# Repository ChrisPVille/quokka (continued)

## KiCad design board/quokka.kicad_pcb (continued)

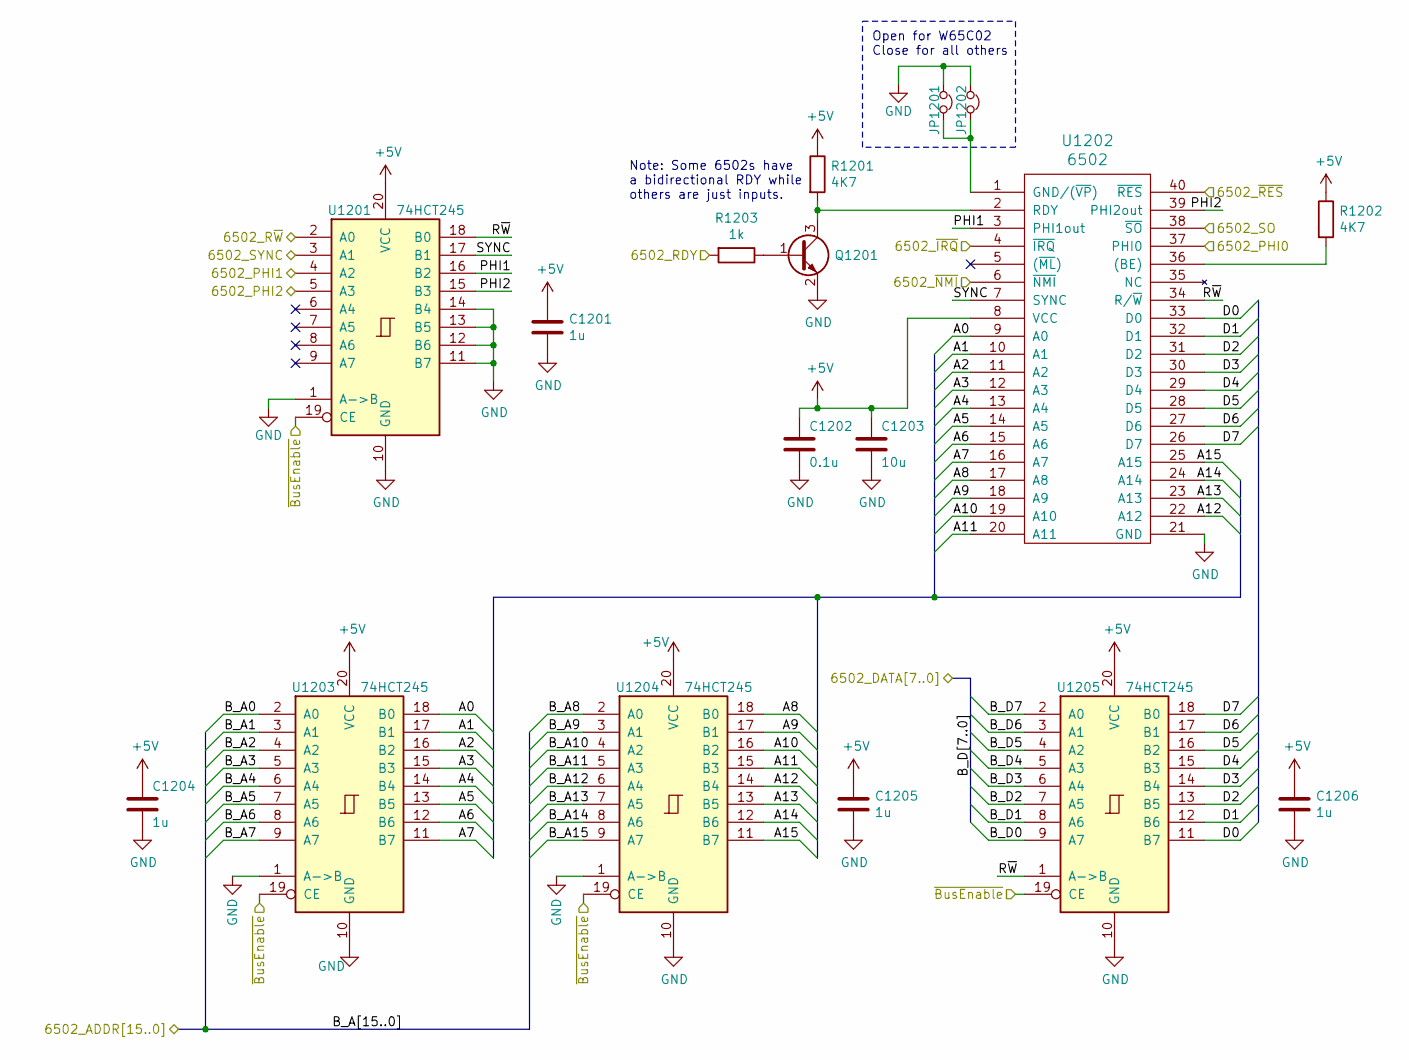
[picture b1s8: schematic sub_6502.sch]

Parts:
C1201, C1204, C1205, C1206: 1u; C_0603_1608Metric
C1202: 0.1u; C_0603_1608Metric
C1203: 10u; C_1206_3216Metric
JP1201: Jumper_NC_Small; PinHeader_1x02_P2.54mm_Vertical
JP1202: WireJumper; PinHeader_1x02_P2.54mm_Vertical
Q1201: Q_NPN_BEC; SOT-23
R1201, R1202: 4K7; R_0603_1608Metric
R1203: 1k; R_0603_1608Metric
U1201, U1203, U1204, U1205: 74HCT245; SSOP-20_4.4x6.5mm_P0.65mm
U1202: 6502; DIP-40_W15.24mm

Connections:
+5V: C1201.1, C1202.1, C1203.1, C1204.1, C1205.1, C1206.1, R1201.1, R1202.1, U1201.20 (VCC), U1202.8 (VCC), U1203.20 (VCC), U1204.20 (VCC), U1205.20 (VCC); also elsewhere on the board
/6502/6502_PHI0: U1202.37 (PHI0); also elsewhere on the board
/6502/6502_PHI1: U1201.4 (A2); also elsewhere on the board
/6502/6502_PHI2: U1201.5 (A3); also elsewhere on the board
/6502/6502_RDY: R1203.2; also elsewhere on the board
/6502/6502_R~W: U1201.2 (A0); also elsewhere on the board
/6502/6502_SO: U1202.38 (~SO); also elsewhere on the board
/6502/6502_SYNC: U1201.3 (A1); also elsewhere on the board
/6502/6502_~IRQ: U1202.4 (~IRQ); also elsewhere on the board
/6502/6502_~NMI: U1202.6 (~NMI); also elsewhere on the board
/6502/6502_~RES: U1202.40 (~RES); also elsewhere on the board
/6502/A0: U1202.9 (A0), U1203.18 (B0)
/6502/A1: U1202.10 (A1), U1203.17 (B1)
/6502/A2: U1202.11 (A2), U1203.16 (B2)
/6502/A3: U1202.12 (A3), U1203.15 (B3)
/6502/A4: U1202.13 (A4), U1203.14 (B4)
/6502/A5: U1202.14 (A5), U1203.13 (B5)
/6502/A6: U1202.15 (A6), U1203.12 (B6)
/6502/A7: U1202.16 (A7), U1203.11 (B7)
/6502/A8: U1202.17 (A8), U1204.18 (B0)
/6502/A9: U1202.18 (A9), U1204.17 (B1)
/6502/A10: U1202.19 (A10), U1204.16 (B2)
/6502/A11: U1202.20 (A11), U1204.15 (B3)
/6502/A12: U1202.22 (A12), U1204.14 (B4)
/6502/A13: U1202.23 (A13), U1204.13 (B5)
/6502/A14: U1202.24 (A14), U1204.12 (B6)
/6502/A15: U1202.25 (A15), U1204.11 (B7)
/6502/B_D0: U1205.9 (A7); also elsewhere on the board
/6502/B_D1: U1205.8 (A6); also elsewhere on the board
/6502/B_D2: U1205.7 (A5); also elsewhere on the board
/6502/B_D3: U1205.6 (A4); also elsewhere on the board
/6502/B_D4: U1205.5 (A3); also elsewhere on the board
/6502/B_D5: U1205.4 (A2); also elsewhere on the board
/6502/B_D6: U1205.3 (A1); also elsewhere on the board
/6502/B_D7: U1205.2 (A0); also elsewhere on the board
/6502/D0: U1202.33 (D0), U1205.11 (B7)
/6502/D1: U1202.32 (D1), U1205.12 (B6)
/6502/D2: U1202.31 (D2), U1205.13 (B5)
/6502/D3: U1202.30 (D3), U1205.14 (B4)
/6502/D4: U1202.29 (D4), U1205.15 (B3)
/6502/D5: U1202.28 (D5), U1205.16 (B2)
/6502/D6: U1202.27 (D6), U1205.17 (B1)
/6502/D7: U1202.26 (D7), U1205.18 (B0)
/6502/PHI1: U1201.16 (B2), U1202.3 (PHI1out)
/6502/PHI2: U1201.15 (B3), U1202.39 (PHI2out)
/6502/R~W: U1201.18 (B0), U1202.34 (R/~W), U1205.1 (A->B)
/6502/SYNC: U1201.17 (B1), U1202.7 (SYNC)
/Bus Expansion/A0: U1203.2 (A0); also elsewhere on the board
/Bus Expansion/A1: U1203.3 (A1); also elsewhere on the board
/Bus Expansion/A2: U1203.4 (A2); also elsewhere on the board
/Bus Expansion/A3: U1203.5 (A3); also elsewhere on the board
/Bus Expansion/A4: U1203.6 (A4); also elsewhere on the board
/Bus Expansion/A5: U1203.7 (A5); also elsewhere on the board
/Bus Expansion/A6: U1203.8 (A6); also elsewhere on the board
/Bus Expansion/A7: U1203.9 (A7); also elsewhere on the board
/Bus Expansion/A8: U1204.2 (A0); also elsewhere on the board
/Bus Expansion/A9: U1204.3 (A1); also elsewhere on the board
/Bus Expansion/A10: U1204.4 (A2); also elsewhere on the board
/Bus Expansion/A11: U1204.5 (A3); also elsewhere on the board
/Bus Expansion/A12: U1204.6 (A4); also elsewhere on the board
/Bus Expansion/A13: U1204.7 (A5); also elsewhere on the board
/Bus Expansion/A14: U1204.8 (A6); also elsewhere on the board
/Bus Expansion/A15: U1204.9 (A7); also elsewhere on the board
/FPGA/Physical6502_~BusEnable: U1201.19 (CE), U1203.19 (CE), U1204.19 (CE), U1205.19 (CE); also elsewhere on the board
GND: C1201.2, C1202.2, C1203.2, C1204.2, C1205.2, C1206.2, JP1201.1, JP1202.1, Q1201.2 (E), U1201.1 (A->B), U1201.10 (GND), U1201.11 (B7), U1201.12 (B6), U1201.13 (B5), U1201.14 (B4), U1202.21 (GND), U1203.1 (A->B), U1203.10 (GND), U1204.1 (A->B), U1204.10 (GND), U1205.10 (GND); also elsewhere on the board
unnamed: JP1201.2, JP1202.2, U1202.1 (GND/(~VP~))
unnamed: Q1201.1 (B), R1203.1
unnamed: Q1201.3 (C), R1201.2, U1202.2 (RDY)
unnamed: R1202.2, U1202.36 ((BE))

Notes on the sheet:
Open for W65C02 Close for all others
Note: Some 6502s have a bidirectional RDY while others are just inputs.

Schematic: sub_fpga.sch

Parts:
C1301: 0.1u; C_0603_1608Metric
J1301: FPGA JTAG; PinHeader_1x06_P2.54mm_Vertical
Q1301: Q_NPN_BEC; SOT-23
R1301, R1304: 4K7; R_0603_1608Metric
R1302: 390; R_0603_1608Metric
R1303, R1306: 68; R_0603_1608Metric
R1305: 1k; R_0603_1608Metric
U205: XC3S200-TQ144; LQFP-144_20x20mm_P0.5mm
X1301: SG7050CAN 25.0Mhz; Oscillator_SMD_SeikoEpson_SG8002CA-4Pin_7.0x5.0mm

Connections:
+2V5: J1301.6, R1302.2, U205.37 (M1), U205.38 (M0), U205.39 (M2); also elsewhere on the board
/Bus Expansion/E0: U205.27 (IO_L22P_6); also elsewhere on the board
/Bus Expansion/E1: U205.28 (IO_L22N_6); also elsewhere on the board
/Bus Expansion/E2: U205.30 (IO_L21P_6); also elsewhere on the board
/Bus Expansion/E3: U205.31 (IO_L21N_6); also elsewhere on the board
/Bus Expansion/E4: U205.32 (IO_L20P_6); also elsewhere on the board
/Bus Expansion/E5: U205.33 (IO_L20N_6); also elsewhere on the board
/Bus Expansion/E6: U205.35 (IO_L01P_6/VRN_6); also elsewhere on the board
/Bus Expansion/E7: U205.36 (IO_L01N_6/VRP_6); also elsewhere on the board
/FPGA/A0: U205.108 (IO_L01N_2/VRP_2); also elsewhere on the board
/FPGA/A1: U205.107 (IO_L01P_2/VRN_2); also elsewhere on the board
/FPGA/A2: U205.105 (IO_L20N_2); also elsewhere on the board
/FPGA/A3: U205.104 (IO_L20P_2); also elsewhere on the board
/FPGA/A4: U205.103 (IO_L21N_2); also elsewhere on the board
/FPGA/A5: U205.102 (IO_L21P_2); also elsewhere on the board
/FPGA/A6: U205.100 (IO_L22N_2); also elsewhere on the board
/FPGA/A7: U205.99 (IO_L22P_2); also elsewhere on the board
/FPGA/A8: U205.98 (IO_L23N_2/VREF_2); also elsewhere on the board
/FPGA/A9: U205.97 (IO_L23P_2); also elsewhere on the board
/FPGA/A10: U205.96 (IO_L24N_2); also elsewhere on the board
/FPGA/A11: U205.95 (IO_L24P_2); also elsewhere on the board
/FPGA/A12: U205.93 (IO_L40N_2); also elsewhere on the board
/FPGA/A13: U205.92 (IO_L40P_2/VREF_2); also elsewhere on the board
/FPGA/A14: U205.90 (IO_L40N_3/VREF_3); also elsewhere on the board
/FPGA/A15: U205.89 (IO_L40P_3); also elsewhere on the board
/FPGA/A16: U205.84 (IO_L23P_3/VREF_3); also elsewhere on the board
/FPGA/A17: U205.85 (IO_L23N_3); also elsewhere on the board
/FPGA/A18: U205.86 (IO_L24P_3); also elsewhere on the board
/FPGA/A19: U205.87 (IO_L24N_3); also elsewhere on the board
/FPGA/C0: U205.12 (IO_L23P_7); also elsewhere on the board
/FPGA/C1: U205.13 (IO_L23N_7); also elsewhere on the board
/FPGA/C2: U205.14 (IO_L24P_7); also elsewhere on the board
/FPGA/C3: U205.15 (IO_L24N_7); also elsewhere on the board
/FPGA/C4: U205.17 (IO_L40P_7); also elsewhere on the board
/FPGA/C5: U205.18 (IO_L40N_7/VREF_7); also elsewhere on the board
/FPGA/D0: U205.73 (IO_L01P_3/VRN_3); also elsewhere on the board
/FPGA/D1: U205.74 (IO_L01N_3/VRP_3); also elsewhere on the board
/FPGA/D2: U205.76 (IO); also elsewhere on the board
/FPGA/D3: U205.77 (IO_L20P_3); also elsewhere on the board
/FPGA/D4: U205.78 (IO_L20N_3); also elsewhere on the board
/FPGA/D5: U205.79 (IO_L21P_3); also elsewhere on the board
/FPGA/D6: U205.80 (IO_L21N_3); also elsewhere on the board
/FPGA/D7: U205.82 (IO_L22P_3); also elsewhere on the board
/FPGA/DataDir: U205.4 (IO/VREF_7); also elsewhere on the board
/FPGA/FPGA_CCLK: R1303.1; also elsewhere on the board
/FPGA/FPGA_CDIN: U205.65 (IO_L27N_4/DIN/D0); also elsewhere on the board
/FPGA/FPGA_DONE: Q1301.3 (C), R1304.2; also elsewhere on the board
/FPGA/FPGA_PROG_B: R1306.1; also elsewhere on the board
/FPGA/FPGA_~INT: U205.60 (IO_L30N_4/D2); also elsewhere on the board
/FPGA/G0: U205.40 (IO_L01P_5/CS_B); also elsewhere on the board
/FPGA/G1: U205.41 (IO_L01N_5/RDWR_B); also elsewhere on the board
/FPGA/G2: U205.44 (IO/VREF_5); also elsewhere on the board
/FPGA/G3: U205.46 (IO_L28P_5/D7); also elsewhere on the board
/FPGA/G4: U205.47 (IO_L28N_5/D6); also elsewhere on the board
/FPGA/G5: U205.50 (IO_L31P_5/D5); also elsewhere on the board
/FPGA/G6: U205.51 (IO_L31N_5/D4); also elsewhere on the board
/FPGA/G7: U205.52 (IO_L32P_5/GCLK2); also elsewhere on the board
/FPGA/GPIO_R~W: U205.55 (IO_L32P_4/GCLK0); also elsewhere on the board
/FPGA/IRQ: U205.130 (IO_L31N_0); also elsewhere on the board
/FPGA/LED_CLK: U205.124 (IO_L32P_1/GCLK4); also elsewhere on the board
/FPGA/LED_DATA: U205.122 (IO_L31P_1); also elsewhere on the board
/FPGA/LED_LOAD: U205.119 (IO_L28N_1); also elsewhere on the board
/FPGA/LED_~CLR: U205.1 (IO_L01P_7/VRN_7); also elsewhere on the board
/FPGA/OPT1_~cs: U205.113 (IO_L01N_1/VRP_1); also elsewhere on the board
/FPGA/OPT2_~cs: U205.118 (IO_L28P_1); also elsewhere on the board
/FPGA/PHI0: U205.125 (IO_L32N_1/GCLK5); also elsewhere on the board
/FPGA/PHI1: U205.127 (IO_L32P_0/GCLK6); also elsewhere on the board
/FPGA/PHI2: U205.128 (IO_L32N_0/GCLK7); also elsewhere on the board
/FPGA/Phys6502_~BusEnable: U205.141 (IO_L01N_0/VRP_0); also elsewhere on the board
/FPGA/Phys6502_~RES: U205.135 (IO_L27P_0); also elsewhere on the board
/FPGA/R0: U205.20 (IO_L40P_6/VREF_6); also elsewhere on the board
/FPGA/R1: U205.21 (IO_L40N_6); also elsewhere on the board
/FPGA/R2: U205.23 (IO_L24P_6); also elsewhere on the board
/FPGA/R3: U205.24 (IO_L24N_6/VREF_6); also elsewhere on the board
/FPGA/R4: U205.25 (IO_L23P_6); also elsewhere on the board
/FPGA/RAM_~cs: U205.112 (IO_L01P_1/VRN_1); also elsewhere on the board
/FPGA/RDY: U205.131 (IO_L30P_0); also elsewhere on the board
/FPGA/RES: U205.137 (IO_L27N_0); also elsewhere on the board
/FPGA/R~W: U205.123 (IO_L31N_1/VREF_1); also elsewhere on the board
/FPGA/SENSE_RES: U205.6 (IO_L20N_7); also elsewhere on the board
/FPGA/SO: U205.140 (IO_L01P_0/VRN_0); also elsewhere on the board
/FPGA/SYNC: U205.129 (IO_L31P_0/VREF_0); also elsewhere on the board
/FPGA/TCK: J1301.4, U205.110 (TCK)
/FPGA/TDI: J1301.2, U205.144 (TDI)
/FPGA/TDO: J1301.3, U205.109 (TDO)
/FPGA/TMS: J1301.1, U205.111 (TMS)
/FPGA/~Drive6502Bus: U205.5 (IO_L20P_7); also elsewhere on the board
/FPGA/~EnableXcvers: U205.2 (IO_L01N_7/VRP_7); also elsewhere on the board
/FPGA/~NMI: U205.132 (IO_L30N_0); also elsewhere on the board
/Flash/MISO: U205.59 (IO_L30P_4/D3); also elsewhere on the board
/Flash/MOSI: U205.57 (IO_L31P_4/DOUT/BUSY); also elsewhere on the board
/Flash/SCLK: U205.56 (IO_L32N_4/GCLK1); also elsewhere on the board
/Microcontroller/FPGA_DONE: R1301.2, U205.58 (IO_L31N_4/INIT_B); also elsewhere on the board
/Microcontroller/SPI_FPGA_~CS: U205.63 (IO_L27P_4/D1); also elsewhere on the board
GND: C1301.2, J1301.5, Q1301.2 (E), U205.142 (HSWAP_EN), X1301.2 (GND); also elsewhere on the board
unnamed: Q1301.1 (B), R1305.1
unnamed: R1302.1, R1305.2, U205.71 (DONE)
unnamed: R1303.2, U205.72 (CCLK)
unnamed: R1306.2, U205.143 (PROG_B)
unnamed: U205.53 (IO_L32N_5/GCLK3), X1301.3 (OUT)

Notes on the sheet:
(3.3V)
(2.5V)

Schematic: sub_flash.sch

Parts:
C1501: 1u; C_0603_1608Metric
R1501, R1502: 4K7; R_0603_1608Metric
U1501: W25Q64JVSSIM; SOIJ-8_5.3x5.3mm_P1.27mm

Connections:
/Flash/MISO: U1501.2 (DO); also elsewhere on the board
/Flash/MOSI: U1501.5 (DI); also elsewhere on the board
/Flash/SCLK: U1501.6 (CLK); also elsewhere on the board
/Microcontroller/SPI_FLASH_~CS: U1501.1 (~CS); also elsewhere on the board
GND: C1501.2, U1501.4 (GND); also elsewhere on the board
unnamed: R1501.2, U1501.7 (~Hold)
unnamed: R1502.1, U1501.3 (~WP)

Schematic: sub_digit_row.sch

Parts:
C601, C602, C603: 1u; C_0603_1608Metric
D601, D602, D603, D604: 14-segment
Q601, Q602, Q603, Q604, Q605, Q606, Q607, Q608: Q_PMOS_GSD; SOT-23
R601, R602, R603, R604, R605, R606, R607, R608: 4K7; R_0603_1608Metric
R609, R610, R611, R612, R613, R614, R615, R616, R617, R618, R619, R620, R621, R622, R623: 160; R_1206_3216Metric
U601, U602, U603: TPIC6D595; SOIC-16_3.9x9.9mm_P1.27mm

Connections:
+5V: C601.1, C602.1, C603.1, Q601.3 (D), Q602.3 (D), Q603.3 (D), Q604.3 (D), Q605.3 (D), Q606.3 (D), Q607.3 (D), Q608.3 (D), R601.1, R602.1, R603.1, R604.1, R605.1, R606.1, R607.1, R608.1, U601.1 (VCC), U602.1 (VCC), U603.1 (VCC); also elsewhere on the board
/Display/CLK: U601.15 (SRCK), U602.15 (SRCK), U603.15 (SRCK); also elsewhere on the board
/Display/Digit Row 2/Din: U601.2 (SER_IN); also elsewhere on the board
/Display/Last Digit Row/Din: U603.9 (SER_OUT); also elsewhere on the board
/FPGA/LEDDisp_LOAD: U601.10 (RCK), U602.10 (RCK), U603.10 (RCK); also elsewhere on the board
/FPGA/LEDDisp_~CLR: U601.7 (~CLR), U602.7 (~CLR), U603.7 (~CLR); also elsewhere on the board
GND: C601.2, C602.2, C603.2, U601.8 (~G), U601.16 (GND), U602.8 (~G), U602.16 (GND), U603.8 (~G), U603.16 (GND); also elsewhere on the board
unnamed: D601.1 (E), D602.1 (E), D603.1 (E), D604.1 (E), R609.2
unnamed: D601.2 (N), D602.2 (N), D603.2 (N), D604.2 (N), R610.2
unnamed: D601.4 (M), D602.4 (M), D603.4 (M), D604.4 (M), R611.2
unnamed: D601.5 (L), D602.5 (L), D603.5 (L), D604.5 (L), R612.2
unnamed: D601.6 (G2), D602.6 (G2), D603.6 (G2), D604.6 (G2), R613.2
unnamed: D601.7 (D), D602.7 (D), D603.7 (D), D604.7 (D), R614.2
unnamed: D601.8 (DP), D602.8 (DP), D603.8 (DP), D604.8 (DP), R615.2
unnamed: D601.9 (C), D602.9 (C), D603.9 (C), D604.9 (C), R616.2
unnamed: D601.10 (B), D602.10 (B), D603.10 (B), D604.10 (B), R617.2
unnamed: D601.11 (DIG2), Q601.2 (S)
unnamed: D601.12 (A), D602.12 (A), D603.12 (A), D604.12 (A), R618.2
unnamed: D601.13 (G1), D602.13 (G1), D603.13 (G1), D604.13 (G1), R619.2
unnamed: D601.14 (K), D602.14 (K), D603.14 (K), D604.14 (K), R620.2
unnamed: D601.15 (J), D602.15 (J), D603.15 (J), D604.15 (J), R621.2
unnamed: D601.16 (DIG1), Q605.2 (S)
unnamed: D601.17 (H), D602.17 (H), D603.17 (H), D604.17 (H), R622.2
unnamed: D601.18 (F), D602.18 (F), D603.18 (F), D604.18 (F), R623.2
unnamed: D602.11 (DIG2), Q602.2 (S)
unnamed: D602.16 (DIG1), Q606.2 (S)
unnamed: D603.11 (DIG2), Q603.2 (S)
unnamed: D603.16 (DIG1), Q607.2 (S)
unnamed: D604.11 (DIG2), Q604.2 (S)
unnamed: D604.16 (DIG1), Q608.2 (S)
unnamed: Q601.1 (G), R601.2, U601.14 (DRAIN7)
unnamed: Q602.1 (G), R602.2, U601.12 (DRAIN5)
unnamed: Q603.1 (G), R603.2, U601.4 (DRAIN1)
unnamed: Q604.1 (G), R604.2, U601.6 (DRAIN3)
unnamed: Q605.1 (G), R605.2, U601.13 (DRAIN6)
unnamed: Q606.1 (G), R606.2, U601.11 (DRAIN4)
unnamed: Q607.1 (G), R607.2, U601.3 (DRAIN0)
unnamed: Q608.1 (G), R608.2, U601.5 (DRAIN2)
unnamed: R609.1, U602.6 (DRAIN3)
unnamed: R610.1, U602.5 (DRAIN2)
unnamed: R611.1, U602.4 (DRAIN1)
unnamed: R612.1, U602.3 (DRAIN0)
unnamed: R613.1, U602.12 (DRAIN5)
unnamed: R614.1, U602.11 (DRAIN4)
unnamed: R615.1, U602.14 (DRAIN7)
unnamed: R616.1, U602.13 (DRAIN6)
unnamed: R617.1, U603.6 (DRAIN3)
unnamed: R618.1, U603.5 (DRAIN2)
unnamed: R619.1, U603.4 (DRAIN1)
unnamed: R620.1, U603.3 (DRAIN0)
unnamed: R621.1, U603.12 (DRAIN5)
unnamed: R622.1, U603.11 (DRAIN4)
unnamed: R623.1, U603.14 (DRAIN7)
unnamed: U601.9 (SER_OUT), U602.2 (SER_IN)
unnamed: U602.9 (SER_OUT), U603.2 (SER_IN)

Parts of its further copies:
C701, C702, C703: 1u; C_0603_1608Metric
D701, D702, D703, D704: 14-segment
Q701, Q702, Q703, Q704, Q705, Q706, Q707, Q708: Q_PMOS_GSD; SOT-23
R701, R702, R703, R704, R705, R706, R707, R708: 4K7; R_0603_1608Metric
R709, R710, R711, R712, R713, R714, R715, R716, R717, R718, R719, R720, R721, R722, R723: 160; R_1206_3216Metric
U701, U702, U703: TPIC6D595; SOIC-16_3.9x9.9mm_P1.27mm

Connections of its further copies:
+5V: C701.1, C702.1, C703.1, Q701.3 (D), Q702.3 (D), Q703.3 (D), Q704.3 (D), Q705.3 (D), Q706.3 (D), Q707.3 (D), Q708.3 (D), R701.1, R702.1, R703.1, R704.1, R705.1, R706.1, R707.1, R708.1, U701.1 (VCC), U702.1 (VCC), U703.1 (VCC); also elsewhere on the board
/Display/CLK: U701.15 (SRCK), U702.15 (SRCK), U703.15 (SRCK); also elsewhere on the board
/Display/Digit Row 2/Din: U703.9 (SER_OUT); also elsewhere on the board
/Display/Din: U701.2 (SER_IN); also elsewhere on the board
/FPGA/LEDDisp_LOAD: U701.10 (RCK), U702.10 (RCK), U703.10 (RCK); also elsewhere on the board
/FPGA/LEDDisp_~CLR: U701.7 (~CLR), U702.7 (~CLR), U703.7 (~CLR); also elsewhere on the board
GND: C701.2, C702.2, C703.2, U701.8 (~G), U701.16 (GND), U702.8 (~G), U702.16 (GND), U703.8 (~G), U703.16 (GND); also elsewhere on the board
unnamed: D701.1 (E), D702.1 (E), D703.1 (E), D704.1 (E), R709.2
unnamed: D701.2 (N), D702.2 (N), D703.2 (N), D704.2 (N), R710.2
unnamed: D701.4 (M), D702.4 (M), D703.4 (M), D704.4 (M), R711.2
unnamed: D701.5 (L), D702.5 (L), D703.5 (L), D704.5 (L), R712.2
unnamed: D701.6 (G2), D702.6 (G2), D703.6 (G2), D704.6 (G2), R713.2
unnamed: D701.7 (D), D702.7 (D), D703.7 (D), D704.7 (D), R714.2
unnamed: D701.8 (DP), D702.8 (DP), D703.8 (DP), D704.8 (DP), R715.2
unnamed: D701.9 (C), D702.9 (C), D703.9 (C), D704.9 (C), R716.2
unnamed: D701.10 (B), D702.10 (B), D703.10 (B), D704.10 (B), R717.2
unnamed: D701.11 (DIG2), Q701.2 (S)
unnamed: D701.12 (A), D702.12 (A), D703.12 (A), D704.12 (A), R718.2
unnamed: D701.13 (G1), D702.13 (G1), D703.13 (G1), D704.13 (G1), R719.2
unnamed: D701.14 (K), D702.14 (K), D703.14 (K), D704.14 (K), R720.2
unnamed: D701.15 (J), D702.15 (J), D703.15 (J), D704.15 (J), R721.2
unnamed: D701.16 (DIG1), Q705.2 (S)
unnamed: D701.17 (H), D702.17 (H), D703.17 (H), D704.17 (H), R722.2
unnamed: D701.18 (F), D702.18 (F), D703.18 (F), D704.18 (F), R723.2
unnamed: D702.11 (DIG2), Q702.2 (S)
unnamed: D702.16 (DIG1), Q706.2 (S)
unnamed: D703.11 (DIG2), Q703.2 (S)
unnamed: D703.16 (DIG1), Q707.2 (S)
unnamed: D704.11 (DIG2), Q704.2 (S)
unnamed: D704.16 (DIG1), Q708.2 (S)
unnamed: Q701.1 (G), R701.2, U701.14 (DRAIN7)
unnamed: Q702.1 (G), R702.2, U701.12 (DRAIN5)
unnamed: Q703.1 (G), R703.2, U701.4 (DRAIN1)
unnamed: Q704.1 (G), R704.2, U701.6 (DRAIN3)
unnamed: Q705.1 (G), R705.2, U701.13 (DRAIN6)
unnamed: Q706.1 (G), R706.2, U701.11 (DRAIN4)
unnamed: Q707.1 (G), R707.2, U701.3 (DRAIN0)
unnamed: Q708.1 (G), R708.2, U701.5 (DRAIN2)
unnamed: R709.1, U702.6 (DRAIN3)
unnamed: R710.1, U702.5 (DRAIN2)
unnamed: R711.1, U702.4 (DRAIN1)
unnamed: R712.1, U702.3 (DRAIN0)
unnamed: R713.1, U702.12 (DRAIN5)
unnamed: R714.1, U702.11 (DRAIN4)
unnamed: R715.1, U702.14 (DRAIN7)
unnamed: R716.1, U702.13 (DRAIN6)
unnamed: R717.1, U703.6 (DRAIN3)
unnamed: R718.1, U703.5 (DRAIN2)
unnamed: R719.1, U703.4 (DRAIN1)
unnamed: R720.1, U703.3 (DRAIN0)
unnamed: R721.1, U703.12 (DRAIN5)
unnamed: R722.1, U703.11 (DRAIN4)
unnamed: R723.1, U703.14 (DRAIN7)
unnamed: U701.9 (SER_OUT), U702.2 (SER_IN)
unnamed: U702.9 (SER_OUT), U703.2 (SER_IN)

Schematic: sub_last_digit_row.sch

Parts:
C801, C802, C803: 1u; C_0603_1608Metric
D801, D802, D803, D804, D805, D806, D807, D808, D809, D810, D811, D812, D813: LED_Small; LED_0805_2012Metric
D817, D818, D819: 14-segment
Q801, Q802, Q803, Q804, Q805, Q806, Q807: Q_PMOS_GSD; SOT-23
R801, R802, R803, R804, R805, R806, R807: 4K7; R_0603_1608Metric
R808, R809, R810, R811, R812, R813, R814, R815, R816, R817, R818, R819, R820, R821, R822: 160; R_1206_3216Metric
U801, U802, U803: TPIC6D595; SOIC-16_3.9x9.9mm_P1.27mm

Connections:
+5V: C801.1, C802.1, C803.1, Q801.3 (D), Q802.3 (D), Q803.3 (D), Q804.3 (D), Q805.3 (D), Q806.3 (D), Q807.3 (D), R801.1, R802.1, R803.1, R804.1, R805.1, R806.1, R807.1, U801.1 (VCC), U802.1 (VCC), U803.1 (VCC); also elsewhere on the board
/Display/CLK: U801.15 (SRCK), U802.15 (SRCK), U803.15 (SRCK); also elsewhere on the board
/Display/Last Digit Row/Din: U801.2 (SER_IN); also elsewhere on the board
/FPGA/LEDDisp_LOAD: U801.10 (RCK), U802.10 (RCK), U803.10 (RCK); also elsewhere on the board
/FPGA/LEDDisp_~CLR: U801.7 (~CLR), U802.7 (~CLR), U803.7 (~CLR); also elsewhere on the board
GND: C801.2, C802.2, C803.2, U801.8 (~G), U801.16 (GND), U802.8 (~G), U802.16 (GND), U803.8 (~G), U803.16 (GND); also elsewhere on the board
unnamed: D801.1 (K), D817.1 (E), D818.1 (E), D819.1 (E), R808.2
unnamed: D801.2 (A), D802.2 (A), D803.2 (A), D804.2 (A), D805.2 (A), D806.2 (A), D807.2 (A), D808.2 (A), D809.2 (A), D810.2 (A), D811.2 (A), D812.2 (A), D813.2 (A), Q807.2 (S)
unnamed: D802.1 (K), D817.2 (N), D818.2 (N), D819.2 (N), R809.2
unnamed: D803.1 (K), D817.4 (M), D818.4 (M), D819.4 (M), R810.2
unnamed: D804.1 (K), D817.5 (L), D818.5 (L), D819.5 (L), R811.2
unnamed: D805.1 (K), D817.6 (G2), D818.6 (G2), D819.6 (G2), R812.2
unnamed: D806.1 (K), D817.7 (D), D818.7 (D), D819.7 (D), R813.2
unnamed: D807.1 (K), D817.8 (DP), D818.8 (DP), D819.8 (DP), R814.2
unnamed: D808.1 (K), D817.9 (C), D818.9 (C), D819.9 (C), R815.2
unnamed: D809.1 (K), D817.10 (B), D818.10 (B), D819.10 (B), R816.2
unnamed: D810.1 (K), D817.12 (A), D818.12 (A), D819.12 (A), R817.2
unnamed: D811.1 (K), D817.13 (G1), D818.13 (G1), D819.13 (G1), R818.2
unnamed: D812.1 (K), D817.14 (K), D818.14 (K), D819.14 (K), R819.2
unnamed: D813.1 (K), D817.15 (J), D818.15 (J), D819.15 (J), R820.2
unnamed: D817.11 (DIG2), Q801.2 (S)
unnamed: D817.16 (DIG1), Q804.2 (S)
unnamed: D817.17 (H), D818.17 (H), D819.17 (H), R821.2
unnamed: D817.18 (F), D818.18 (F), D819.18 (F), R822.2
unnamed: D818.11 (DIG2), Q802.2 (S)
unnamed: D818.16 (DIG1), Q805.2 (S)
unnamed: D819.11 (DIG2), Q803.2 (S)
unnamed: D819.16 (DIG1), Q806.2 (S)
unnamed: Q801.1 (G), R801.2, U801.14 (DRAIN7)
unnamed: Q802.1 (G), R802.2, U801.12 (DRAIN5)
unnamed: Q803.1 (G), R803.2, U801.4 (DRAIN1)
unnamed: Q804.1 (G), R804.2, U801.13 (DRAIN6)
unnamed: Q805.1 (G), R805.2, U801.11 (DRAIN4)
unnamed: Q806.1 (G), R806.2, U801.3 (DRAIN0)
unnamed: Q807.1 (G), R807.2, U801.5 (DRAIN2), U801.6 (DRAIN3)
unnamed: R808.1, U802.6 (DRAIN3)
unnamed: R809.1, U802.5 (DRAIN2)
unnamed: R810.1, U802.4 (DRAIN1)
unnamed: R811.1, U802.3 (DRAIN0)
unnamed: R812.1, U802.12 (DRAIN5)
unnamed: R813.1, U802.11 (DRAIN4)
unnamed: R814.1, U802.14 (DRAIN7)
unnamed: R815.1, U802.13 (DRAIN6)
unnamed: R816.1, U803.6 (DRAIN3)
unnamed: R817.1, U803.5 (DRAIN2)
unnamed: R818.1, U803.4 (DRAIN1)
unnamed: R819.1, U803.3 (DRAIN0)
unnamed: R820.1, U803.12 (DRAIN5)
unnamed: R821.1, U803.11 (DRAIN4)
unnamed: R822.1, U803.14 (DRAIN7)
unnamed: U801.9 (SER_OUT), U802.2 (SER_IN)
unnamed: U802.9 (SER_OUT), U803.2 (SER_IN)

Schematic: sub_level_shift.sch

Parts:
C1401, C1402, C1403, C1404, C1405, C1406, C1407, C1408, C1409, C1410, C1411, C1412, C1413, C1414: 1u; C_0603_1608Metric
Q1401, Q1402, Q1403: Q_NPN_BEC; SOT-23
R1401, R1403, R1405, R1406, R1407: 4K7; R_0603_1608Metric
R1402, R1404: 1k; R_0603_1608Metric
U1401, U1402, U1403, U1404, U1405, U1406, U1407: 74LVC4245A; TSSOP-24_4.4x7.8mm_P0.65mm

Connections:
+5V: C1401.1, C1402.1, C1403.1, C1404.1, C1405.1, C1406.1, C1407.1, R1401.1, R1403.1, R1407.1, U1401.1 (VCCA), U1402.1 (VCCA), U1403.1 (VCCA), U1404.1 (VCCA), U1405.1 (VCCA), U1406.1 (VCCA), U1407.1 (VCCA); also elsewhere on the board
/6502/6502_PHI0: U1402.3 (A0); also elsewhere on the board
/6502/6502_PHI1: U1406.3 (A0); also elsewhere on the board
/6502/6502_PHI2: U1406.4 (A1); also elsewhere on the board
/6502/6502_RDY: U1402.5 (A2); also elsewhere on the board
/6502/6502_R~W: U1406.5 (A2); also elsewhere on the board
/6502/6502_SO: U1402.9 (A6); also elsewhere on the board
/6502/6502_SYNC: U1406.6 (A3); also elsewhere on the board
/6502/6502_~IRQ: Q1402.3 (C), R1403.2; also elsewhere on the board
/6502/6502_~NMI: U1402.6 (A3); also elsewhere on the board
/6502/6502_~RES: U1402.7 (A4); also elsewhere on the board
/6502/B_D0: U1403.3 (A0); also elsewhere on the board
/6502/B_D1: U1403.4 (A1); also elsewhere on the board
/6502/B_D2: U1403.5 (A2); also elsewhere on the board
/6502/B_D3: U1403.6 (A3); also elsewhere on the board
/6502/B_D4: U1403.7 (A4); also elsewhere on the board
/6502/B_D5: U1403.8 (A5); also elsewhere on the board
/6502/B_D6: U1403.9 (A6); also elsewhere on the board
/6502/B_D7: U1403.10 (A7); also elsewhere on the board
/Bus Expansion/6502_OPT1_~cs: U1405.4 (A1); also elsewhere on the board
/Bus Expansion/6502_OPT2_~cs: U1405.5 (A2); also elsewhere on the board
/Bus Expansion/6502_~RES: Q1401.3 (C), R1401.2, R1406.2; also elsewhere on the board
/Bus Expansion/A0: U1404.10 (A7); also elsewhere on the board
/Bus Expansion/A1: U1404.9 (A6); also elsewhere on the board
/Bus Expansion/A2: U1404.8 (A5); also elsewhere on the board
/Bus Expansion/A3: U1404.7 (A4); also elsewhere on the board
/Bus Expansion/A4: U1404.6 (A3); also elsewhere on the board
/Bus Expansion/A5: U1404.5 (A2); also elsewhere on the board
/Bus Expansion/A6: U1404.4 (A1); also elsewhere on the board
/Bus Expansion/A7: U1404.3 (A0); also elsewhere on the board
/Bus Expansion/A8: U1401.10 (A7); also elsewhere on the board
/Bus Expansion/A9: U1401.9 (A6); also elsewhere on the board
/Bus Expansion/A10: U1401.8 (A5); also elsewhere on the board
/Bus Expansion/A11: U1401.7 (A4); also elsewhere on the board
/Bus Expansion/A12: U1401.6 (A3); also elsewhere on the board
/Bus Expansion/A13: U1401.5 (A2); also elsewhere on the board
/Bus Expansion/A14: U1401.4 (A1); also elsewhere on the board
/Bus Expansion/A15: U1401.3 (A0); also elsewhere on the board
/Bus Expansion/A16: U1407.3 (A0); also elsewhere on the board
/Bus Expansion/A17: U1407.4 (A1); also elsewhere on the board
/Bus Expansion/A18: U1407.5 (A2); also elsewhere on the board
/Bus Expansion/A19: U1407.6 (A3); also elsewhere on the board
/Display/CLK: U1405.9 (A6); also elsewhere on the board
/Display/Din: U1405.7 (A4); also elsewhere on the board
/FPGA/6502_RAM_~cs: U1405.3 (A0); also elsewhere on the board
/FPGA/A0: U1404.14 (B7); also elsewhere on the board
/FPGA/A1: U1404.15 (B6); also elsewhere on the board
/FPGA/A2: U1404.16 (B5); also elsewhere on the board
/FPGA/A3: U1404.17 (B4); also elsewhere on the board
/FPGA/A4: U1404.18 (B3); also elsewhere on the board
/FPGA/A5: U1404.19 (B2); also elsewhere on the board
/FPGA/A6: U1404.20 (B1); also elsewhere on the board
/FPGA/A7: U1404.21 (B0); also elsewhere on the board
/FPGA/A8: U1401.14 (B7); also elsewhere on the board
/FPGA/A9: U1401.15 (B6); also elsewhere on the board
/FPGA/A10: U1401.16 (B5); also elsewhere on the board
/FPGA/A11: U1401.17 (B4); also elsewhere on the board
/FPGA/A12: U1401.18 (B3); also elsewhere on the board
/FPGA/A13: U1401.19 (B2); also elsewhere on the board
/FPGA/A14: U1401.20 (B1); also elsewhere on the board
/FPGA/A15: U1401.21 (B0); also elsewhere on the board
/FPGA/A16: U1407.21 (B0); also elsewhere on the board
/FPGA/A17: U1407.20 (B1); also elsewhere on the board
/FPGA/A18: U1407.19 (B2); also elsewhere on the board
/FPGA/A19: U1407.18 (B3); also elsewhere on the board
/FPGA/D0: U1403.21 (B0); also elsewhere on the board
/FPGA/D1: U1403.20 (B1); also elsewhere on the board
/FPGA/D2: U1403.19 (B2); also elsewhere on the board
/FPGA/D3: U1403.18 (B3); also elsewhere on the board
/FPGA/D4: U1403.17 (B4); also elsewhere on the board
/FPGA/D5: U1403.16 (B5); also elsewhere on the board
/FPGA/D6: U1403.15 (B6); also elsewhere on the board
/FPGA/D7: U1403.14 (B7); also elsewhere on the board
/FPGA/DataDir: U1403.2 (A->B); also elsewhere on the board
/FPGA/IRQ: U1402.20 (B1); also elsewhere on the board
/FPGA/LEDDisp_LOAD: U1405.6 (A3); also elsewhere on the board
/FPGA/LEDDisp_~CLR: U1405.8 (A5); also elsewhere on the board
/FPGA/LED_CLK: U1405.15 (B6); also elsewhere on the board
/FPGA/LED_DATA: U1405.17 (B4); also elsewhere on the board
/FPGA/LED_LOAD: U1405.18 (B3); also elsewhere on the board
/FPGA/LED_~CLR: U1405.16 (B5); also elsewhere on the board
/FPGA/Level Converters/IRQ: R1404.2, U1402.4 (A1)
/FPGA/Level Converters/RES: R1402.2, U1402.8 (A5)
/FPGA/OPT1_~cs: U1405.20 (B1); also elsewhere on the board
/FPGA/OPT2_~cs: U1405.19 (B2); also elsewhere on the board
/FPGA/PHI0: U1402.21 (B0); also elsewhere on the board
/FPGA/PHI1: U1406.21 (B0); also elsewhere on the board
/FPGA/PHI2: U1406.20 (B1); also elsewhere on the board
/FPGA/Phys6502_~BusEnable: U1402.14 (B7); also elsewhere on the board
/FPGA/Phys6502_~RES: U1402.17 (B4); also elsewhere on the board
/FPGA/Physical6502_~BusEnable: R1407.2, U1402.10 (A7); also elsewhere on the board
/FPGA/RAM_~cs: U1405.21 (B0); also elsewhere on the board
/FPGA/RDY: U1402.19 (B2); also elsewhere on the board
/FPGA/RES: U1402.16 (B5); also elsewhere on the board
/FPGA/R~W: U1406.19 (B2); also elsewhere on the board
/FPGA/SENSE_RES: Q1403.3 (C), R1405.2; also elsewhere on the board
/FPGA/SO: U1402.15 (B6); also elsewhere on the board
/FPGA/SYNC: U1406.18 (B3); also elsewhere on the board
/FPGA/~Drive6502Bus: U1401.2 (A->B), U1404.2 (A->B), U1406.2 (A->B); also elsewhere on the board
/FPGA/~EnableXcvers: U1401.22 (CE), U1402.22 (CE), U1403.22 (CE), U1404.22 (CE), U1405.22 (CE), U1406.22 (CE), U1407.22 (CE); also elsewhere on the board
/FPGA/~NMI: U1402.18 (B3); also elsewhere on the board
GND: C1401.2, C1402.2, C1403.2, C1404.2, C1405.2, C1406.2, C1407.2, C1408.2, C1409.2, C1410.2, C1411.2, C1412.2, C1413.2, C1414.2, Q1401.2 (E), Q1402.2 (E), Q1403.2 (E), U1401.11 (GND), U1401.12 (GND), U1401.13 (GND), U1402.2 (A->B), U1402.11 (GND), U1402.12 (GND), U1402.13 (GND), U1403.11 (GND), U1403.12 (GND), U1403.13 (GND), U1404.11 (GND), U1404.12 (GND), U1404.13 (GND), U1405.2 (A->B), U1405.11 (GND), U1405.12 (GND), U1405.13 (GND), U1405.14 (B7), U1406.11 (GND), U1406.12 (GND), U1406.13 (GND), U1407.2 (A->B), U1407.11 (GND), U1407.12 (GND), U1407.13 (GND), U1407.14 (B7), U1407.15 (B6), U1407.16 (B5), U1407.17 (B4); also elsewhere on the board
unnamed: Q1401.1 (B), R1402.1
unnamed: Q1402.1 (B), R1404.1
unnamed: Q1403.1 (B), R1406.1

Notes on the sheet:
Always inputs (except when using soft-6502)
Always outputs
Bidirectional Data

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
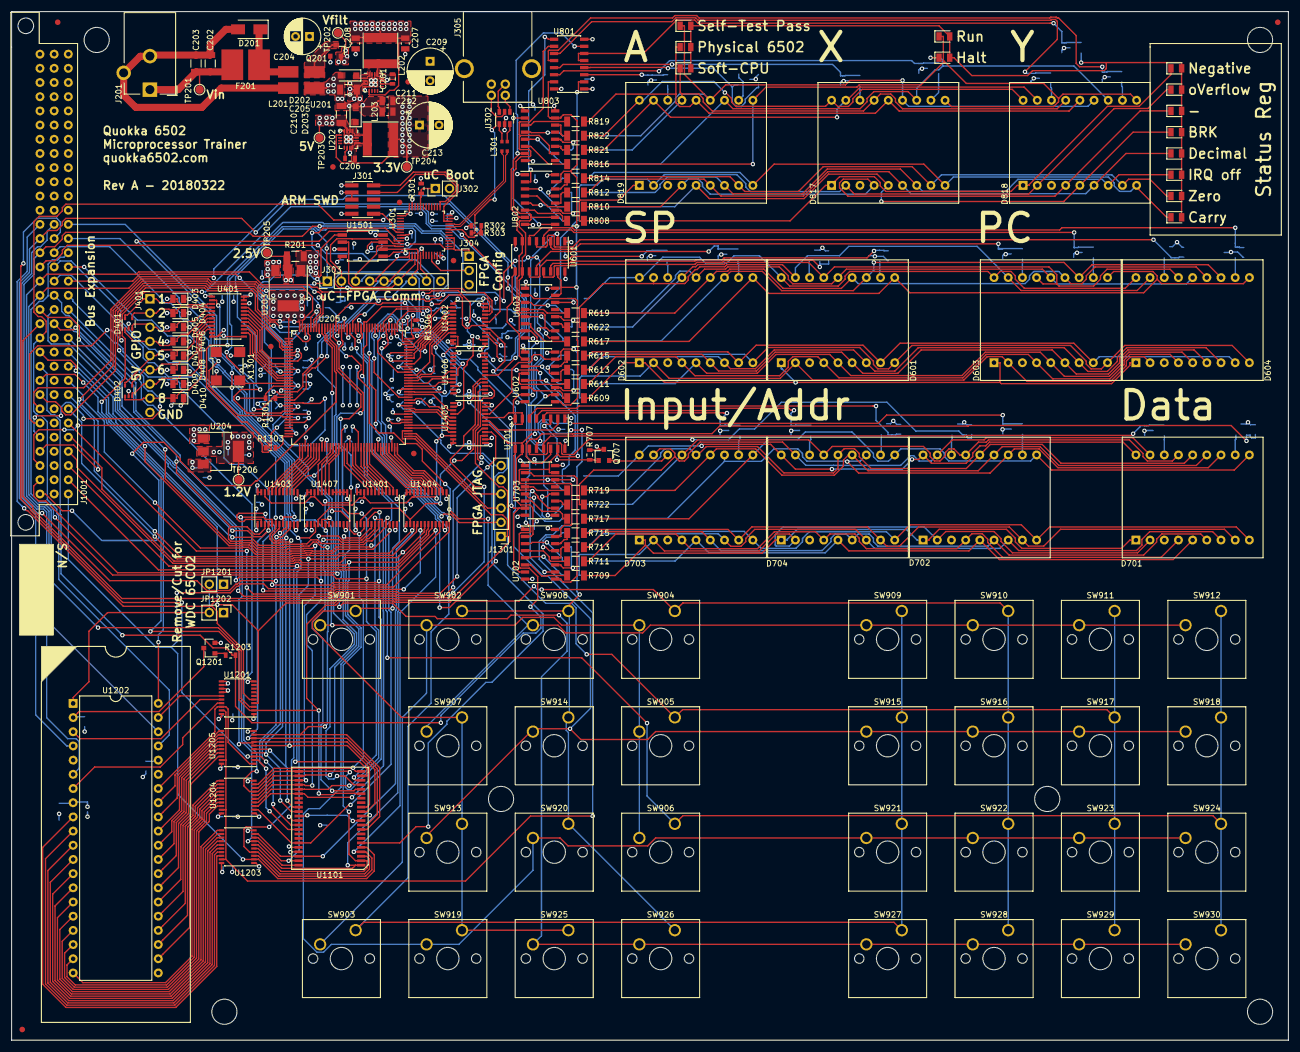
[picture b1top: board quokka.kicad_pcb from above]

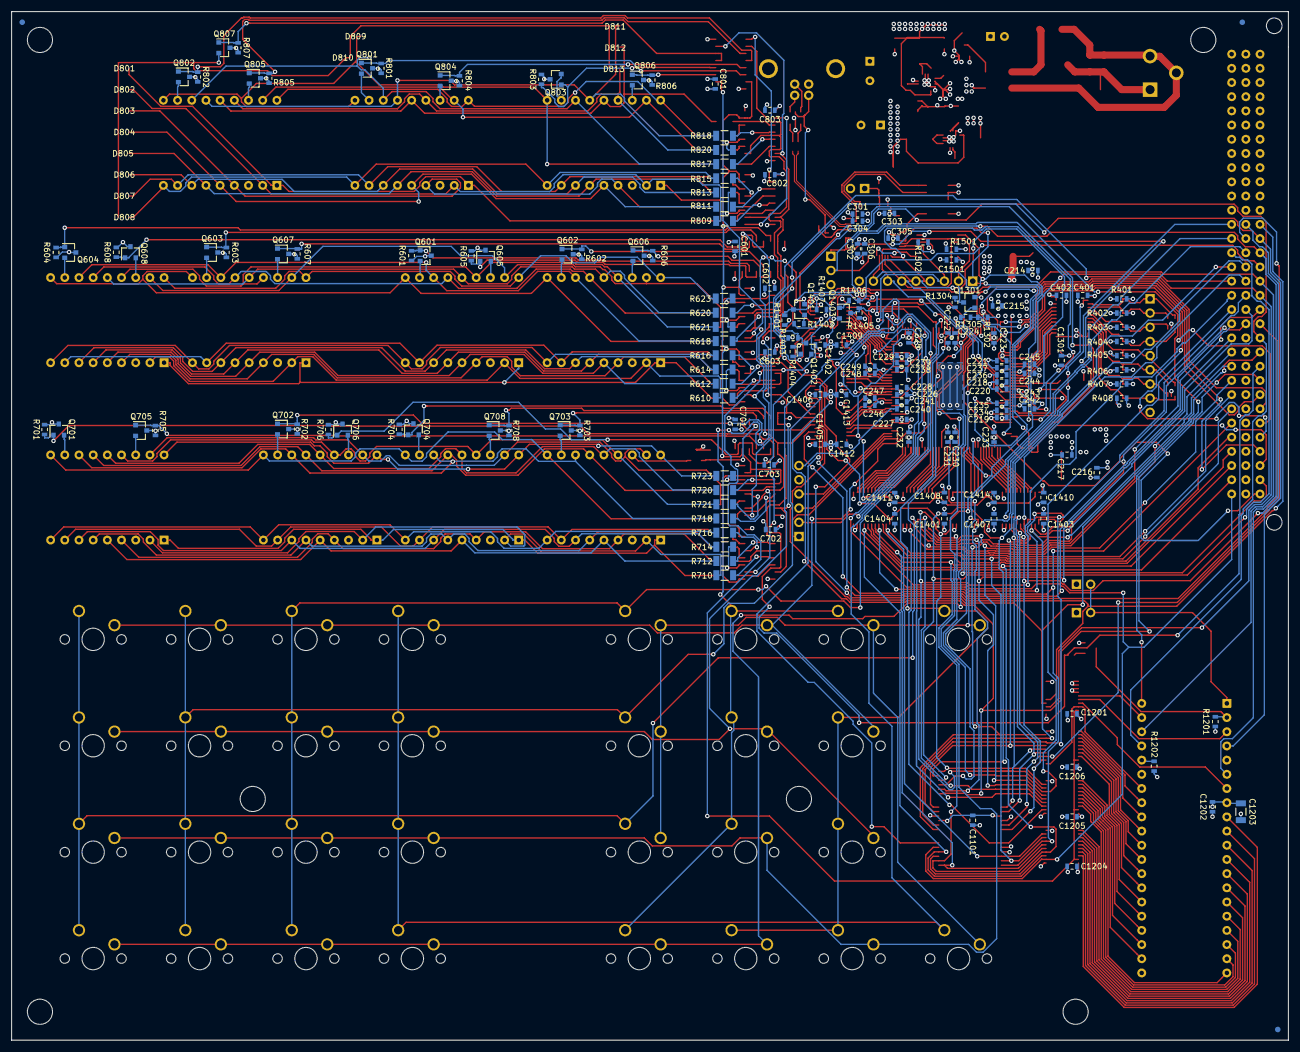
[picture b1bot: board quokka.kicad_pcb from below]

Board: 4 copper layers, 228.6 x 184.1 mm, 355 parts (169 on the bottom side), 371 nets.
